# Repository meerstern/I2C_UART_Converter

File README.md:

# I2C_UART_Converter
I2C-UART Converter with Grove Connector

## 概要 
  * マイコンのI2CポートをUART通信ポートに変換するアダプタです
  * マイコンからI2Cデバイスとして制御し、UARTのボーレート設定、送信、受信処理をすることができます
  * I2C/UARTプロトコルブリッジ[SC16IS740][1]を搭載しています
  * I2CはGrove互換コネクタとなっており、3.3V/５Vの電源、通信に対応しています
  * I2C/UARTプロトコルブリッジSC16IS740は64bytesのバッファを内蔵しています
  * 7.3728MHzの水晶発振子を搭載しており、マイコンのメインクロックから独立してUARTのボーレート設定ができます  
  * デフォルトI2Cアドレスは8bit:0x9A(7bit:0x4D)です  

## 注意 
  * Arduino Uno以外の場合はサンプルコード内SC16IS750.cppの29行目付近のWire定義を必要に応じて変更してください  

## 販売サイト
  * [スイッチサイエンス][2]

[1]: https://www.nxp.com/products/peripherals-and-logic/signal-chain/bridges/single-uart-with-i2c-bus-spi-interface-64-bytes-of-transmit-and-receive-fifos-irda-sir-built-in-support:SC16IS740_750_760 "*1"
[2]: https://www.switch-science.com/products/6027
MIT Lisense

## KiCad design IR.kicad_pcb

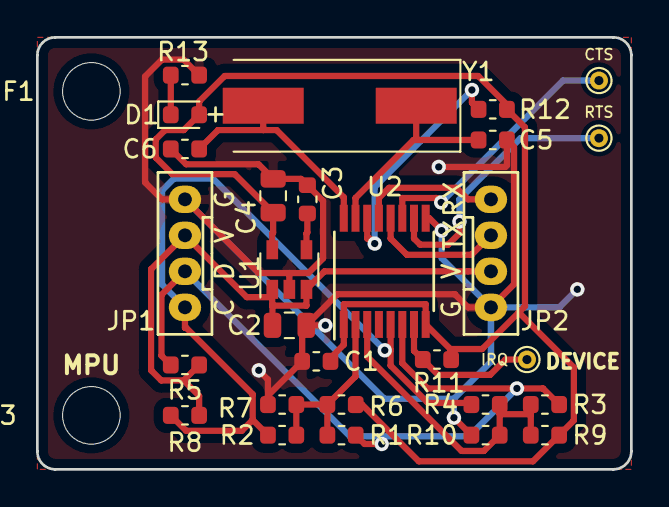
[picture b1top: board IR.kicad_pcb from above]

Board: 2 copper layers, 33.0 x 24.0 mm, 30 parts (0 on the bottom side), 17 nets.

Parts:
C1: 0.1u; C_0603_1608Metric
C2, C4: 10u; C_0805_2012Metric
C3: 0.01u; C_0603_1608Metric
C5, C6: 10p; C_0603_1608Metric
CTS: CTS; TestPoint_THTPad_D1.0mm_Drill0.5mm
D1: LED; D_0603_1608Metric
IRQ: IRQ; TestPoint_THTPad_D1.0mm_Drill0.5mm
JP1, JP2: PINHD-1X4; GROVE
R1, R2, R3, R4, R6, R7, R9, R10: 0; R_0603_1608Metric
R5, R8, R12: 4.7k; R_0603_1608Metric
R11, R13: 1k; R_0603_1608Metric
REF1, REF3: MountingHole_3.2mm_M3
RTS: RTS; TestPoint_THTPad_D1.0mm_Drill0.5mm
U1: LD3985M33R_SOT23; SOT-23-5
U2: SC16IS740IPW; TSSOP-16_4.4x5mm_Pitch0.65mm
Y1: Crystal; Crystal_SMD_HC49-SD

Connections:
/3.3V: C1.1, C4.1, D1.2, R6.1, R9.1, R11.1, R12.1, U1.5, U2.1, U2.8
/5V: C2.1, JP1.3, JP2.3, R5.1, R8.1, U1.1, U1.3
/A0: R1.2, R2.2, R6.2, R7.2, U2.2
/A1: R3.2, R4.2, R9.2, R10.2, U2.3
/IRQ: IRQ.1, R11.2, U2.7
/RST: R12.2, U2.14
/RX: JP2.1, U2.13
/SCL: JP1.1, R2.1, R4.1, R8.2, U2.5
/SDA: JP1.2, R1.1, R3.1, R5.2, U2.6
/TX: JP2.2, U2.12
/XTAL1: C5.1, U2.15, Y1.1
/XTAL2: C6.1, U2.16, Y1.2
GND: C1.2, C2.2, C3.2, C4.2, C5.2, C6.2, JP1.4, JP2.4, R7.1, R10.1, R13.2, U1.2, U2.9
unnamed: C3.1, U1.4
unnamed: D1.1, R13.1
unnamed: RTS.1, U2.10
unnamed: CTS.1, U2.11

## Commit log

2019-11-09 Upload data
2019-11-09 Add Readme
2019-11-09 Add sample code
2019-12-10 Add images
2020-11-01 Update circuit
